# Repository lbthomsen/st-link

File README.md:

# st-link

No longer maintained!

Work in progress - see: https://stm32world.com/wiki/DIY_ST-Link_V2.1

STM32 Programmer.  Should be compatible with ST's ST-Link/V2.1 devices.

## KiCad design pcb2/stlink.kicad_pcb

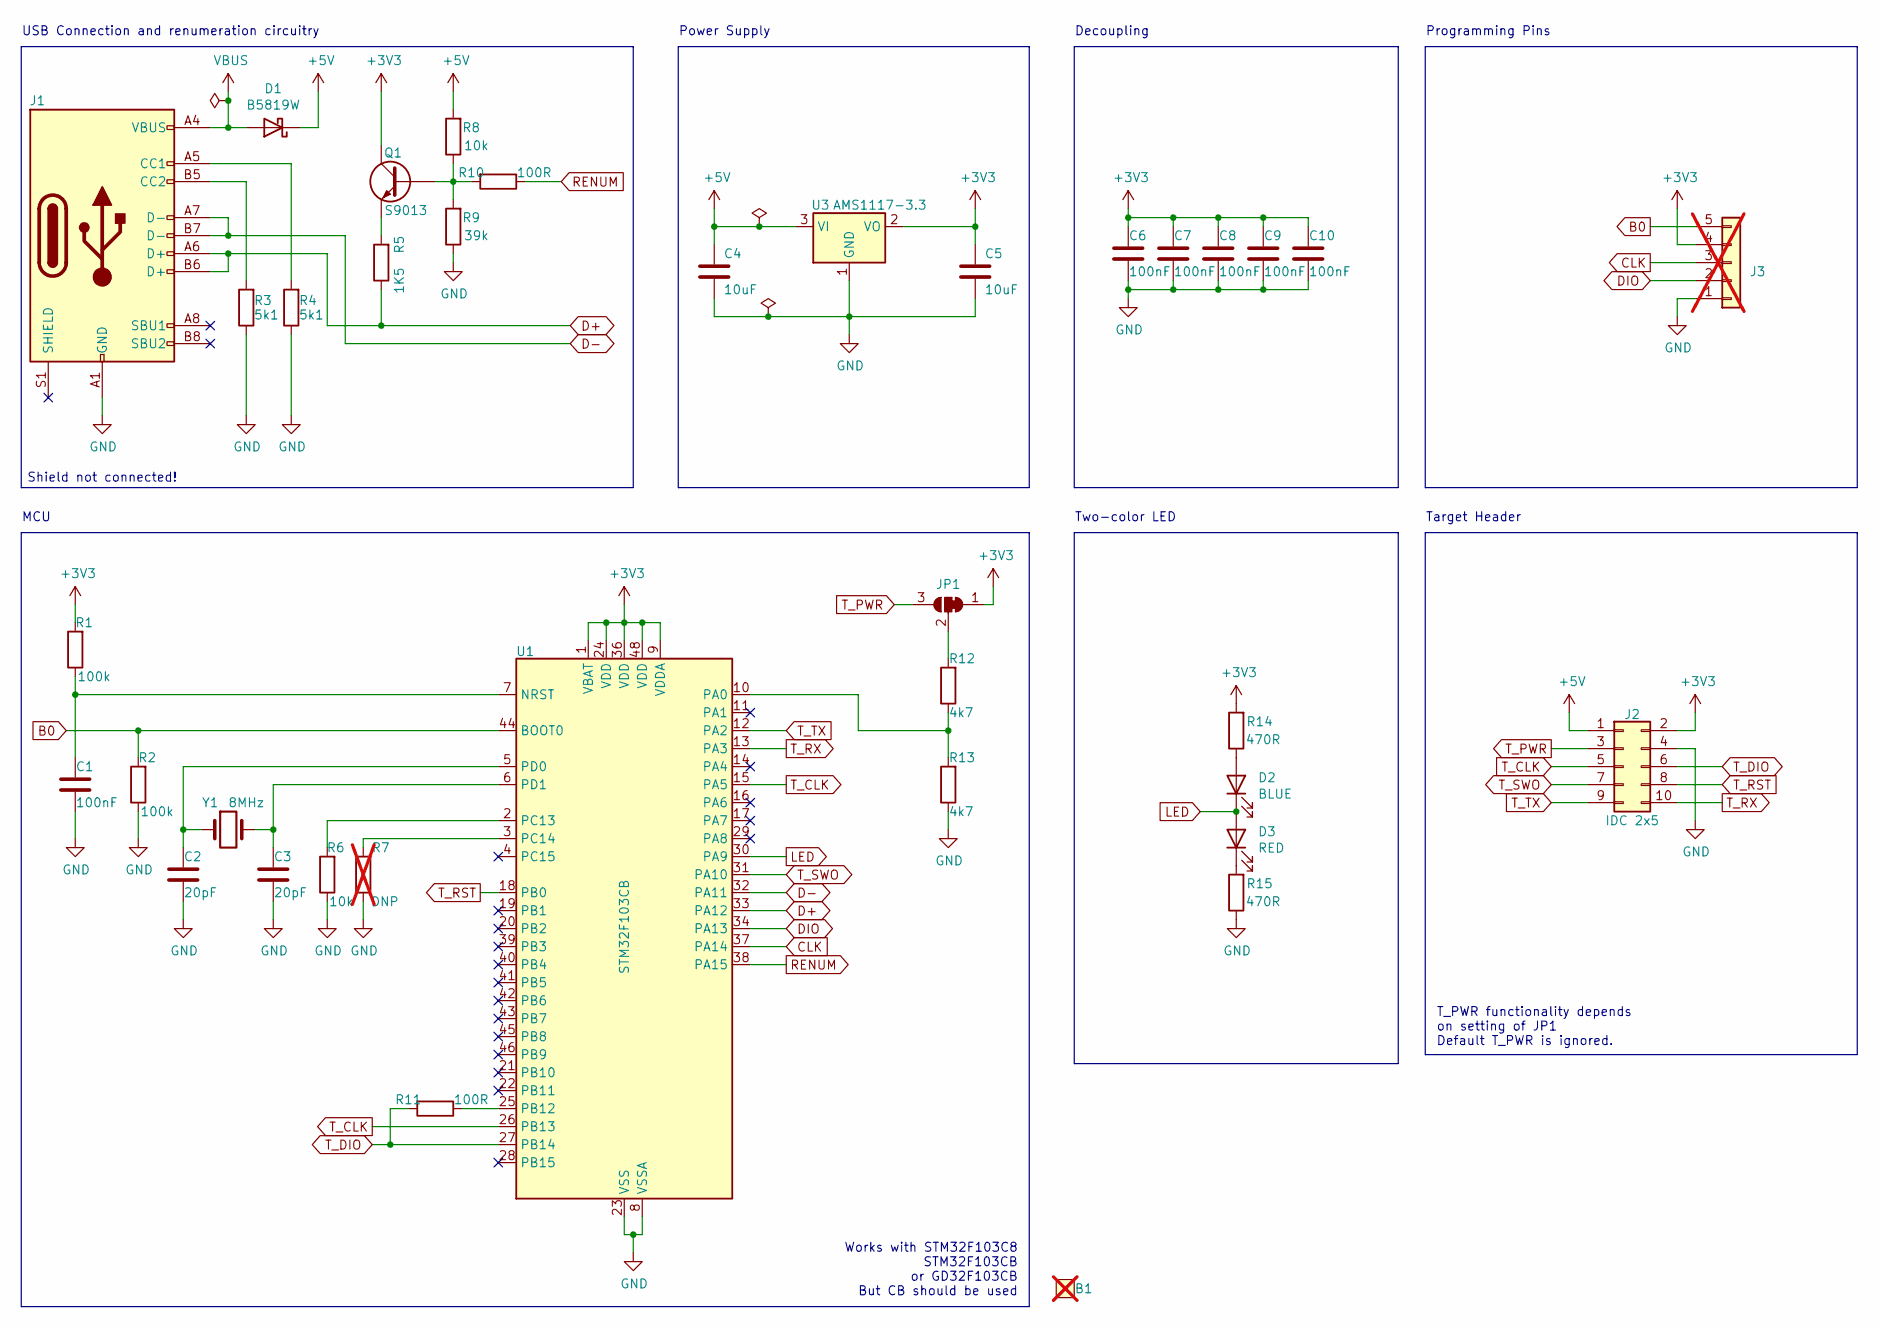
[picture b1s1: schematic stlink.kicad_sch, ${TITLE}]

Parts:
B1: BOARD; not fitted
C1, C6, C7, C8, C9, C10: 100nF; C_0402_1005Metric; LCSC C1525
C2, C3: 20pF; C_0402_1005Metric; LCSC C1554
C4, C5: 10uF; C_0805_2012Metric; LCSC C15850
D1: B5819W; D_SOD-123; LCSC C8598
D2: BLUE; LED_0603_1608Metric; LCSC C72041
D3: RED; LED_0603_1608Metric; LCSC C2286
J1: USB_C_Receptacle_USB2.0-Connector; USB_C_Receptacle_HRO_TYPE-C-31-M-12; LCSC C165948
J2: IDC 2x5; IDC-Header_2x05_P2.54mm_Vertical_SMD; LCSC C41376028
J3: Conn_01x05; PinHeader_1x05_P2.54mm_Vertical; not fitted
JP1: SolderJumper3; SolderJumper-3_P1.3mm_Bridged12_Pad1.0x1.5mm
Q1: S9013; SOT-23; LCSC C6749
R1, R2: 100k; R_0402_1005Metric; LCSC C25741
R3, R4: 5k1; R_0402_1005Metric; LCSC C25905
R5: 1K5; R_0402_1005Metric; LCSC C25867
R6, R8: 10k; R_0402_1005Metric; LCSC C25744
R7: DNP; R_0402_1005Metric; LCSC xxC25744; not fitted
R9: 39k; R_0402_1005Metric; LCSC C25783
R10, R11: 100R; R_0402_1005Metric; LCSC C25076
R12, R13: 4k7; R_0402_1005Metric; LCSC C25900
R14, R15: 470R; R_0402_1005Metric; LCSC C25117
U1: STM32F103CB; LQFP-48_7x7mm_P0.5mm; LCSC C8304
U3: AMS1117-3.3; SOT-223-3_TabPin2; LCSC C6186
Y1: 8MHz; Crystal_SMD_5032-2Pin_5.0x3.2mm; LCSC C115962

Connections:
+3V3: C5.1, C6.1, C7.1, C8.1, C9.1, C10.1, J2.2, J3.4, JP1.1 (A), Q1.C, R1.2, R14.2, U1.1 (VBAT), U1.9 (VDDA), U1.24 (VDD), U1.36 (VDD), U1.48 (VDD), U3.2 (VO)
+5V: C4.1, D1.1 (K), J2.1, R8.2, U3.3 (VI)
B0: J3.5, R2.2, U1.44 (BOOT0)
CLK: J3.3, U1.37 (PA14)
D+: J1.A6 (D+), J1.B6 (D+), R5.1, U1.33 (PA12)
D-: J1.A7 (D-), J1.B7 (D-), U1.32 (PA11)
DIO: J3.2, U1.34 (PA13)
GND: C1.2, C2.2, C3.2, C4.2, C5.2, C6.2, C7.2, C8.2, C9.2, C10.2, J1.A1 (GND), J1.A12 (GND), J1.B1 (GND), J1.B12 (GND), J2.4, J3.1, R2.1, R3.1, R4.1, R6.1, R7.1, R9.1, R13.1, R15.1, U1.8 (VSSA), U1.23 (VSS), U1.35 (VSS), U1.47 (VSS), U3.1 (GND)
LED: D2.1 (K), D3.2 (A), U1.30 (PA9)
unnamed: D2.2 (A), R14.1
unnamed: D3.1 (K), R15.2
unnamed: J1.A5 (CC1), R4.2
unnamed: J1.B5 (CC2), R3.2
unnamed: JP1.2 (C), R12.2
unnamed: Q1.B, R8.1, R9.2, R10.2
unnamed: Q1.E, R5.2
unnamed: C1.1, R1.1, U1.7 (NRST)
unnamed: R12.1, R13.2, U1.10 (PA0)
unnamed: R11.1, U1.25 (PB12)
unnamed: R6.2, U1.2 (PC13)
unnamed: R7.2, U1.3 (PC14)
unnamed: C2.1, U1.5 (PD0), Y1.1
unnamed: C3.1, U1.6 (PD1), Y1.2
RENUM: R10.1, U1.38 (PA15)
T_CLK: J2.5, U1.15 (PA5), U1.26 (PB13)
T_DIO: J2.6, R11.2, U1.27 (PB14)
T_PWR: J2.3, JP1.3 (B)
T_RST: J2.8, U1.18 (PB0)
T_RX: J2.10, U1.13 (PA3)
T_SWO: J2.7, U1.31 (PA10)
T_TX: J2.9, U1.12 (PA2)
VBUS: D1.2 (A), J1.A4 (VBUS), J1.A9 (VBUS), J1.B4 (VBUS), J1.B9 (VBUS)

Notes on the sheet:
Power Supply
T_PWR functionality depends on setting of JP1 Default T_PWR is ignored.
Decoupling
USB Connection and renumeration circuitry
Programming Pins
Target Header
Works with STM32F103C8 STM32F103CB or GD32F103CB But CB should be used
Two-color LED
MCU
Shield not connected!

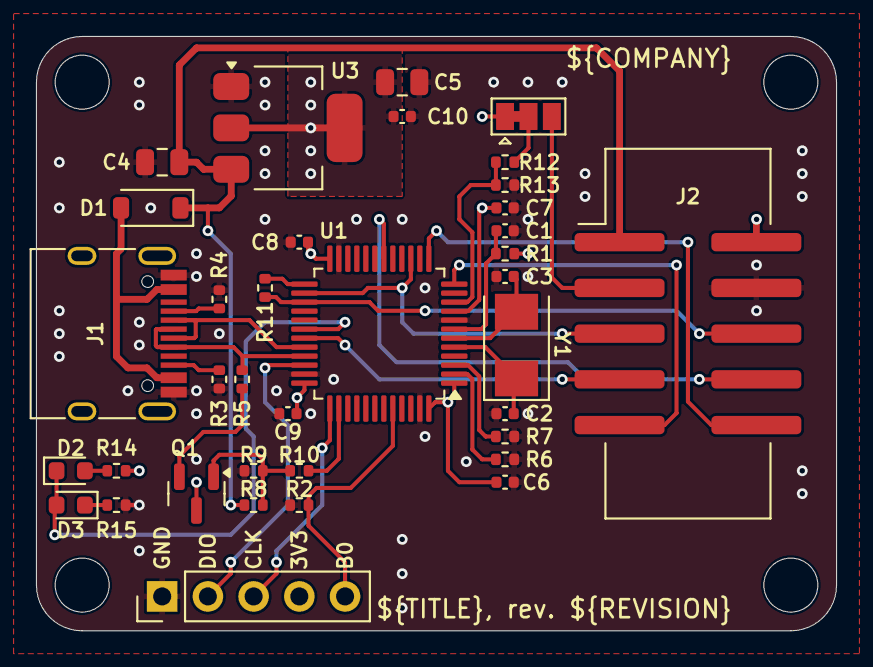
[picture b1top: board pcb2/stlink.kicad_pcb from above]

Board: 4 copper layers, 44.5 x 33.0 mm, 37 parts (0 on the bottom side), 32 nets.

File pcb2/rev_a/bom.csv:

"Reference","Value","Qty","LCSC"
"C1,C6,C7,C8,C9,C10","100nF","6","C1525"
"C2,C3","20pF","2","C1554"
"C4,C5","10uF","2","C15850"
"D1","B5819W","1","C8598"
"D2","BLUE","1","C72041"
"D3","RED","1","C2286"
"J1","USB_C_Receptacle_USB2.0-Connector","1","C165948"
"J2","IDC 2x5","1","C41376028"
"Q1","S9013","1","C6749"
"R1,R2","100k","2","C25741"
"R3,R4","5k1","2","C25905"
"R5","1K5","1","C25867"
"R6,R8","10k","2","C25744"
"R9","39k","1","C25783"
"R10,R11","100R","2","C25076"
"R12,R13","4k7","2","C25900"
"R14,R15","220R","2","C25091"
"U1","STM32F103CB","1","C8304"
"U3","AMS1117-3.3","1","C6186"
"Y1","8MHz","1","C115962"

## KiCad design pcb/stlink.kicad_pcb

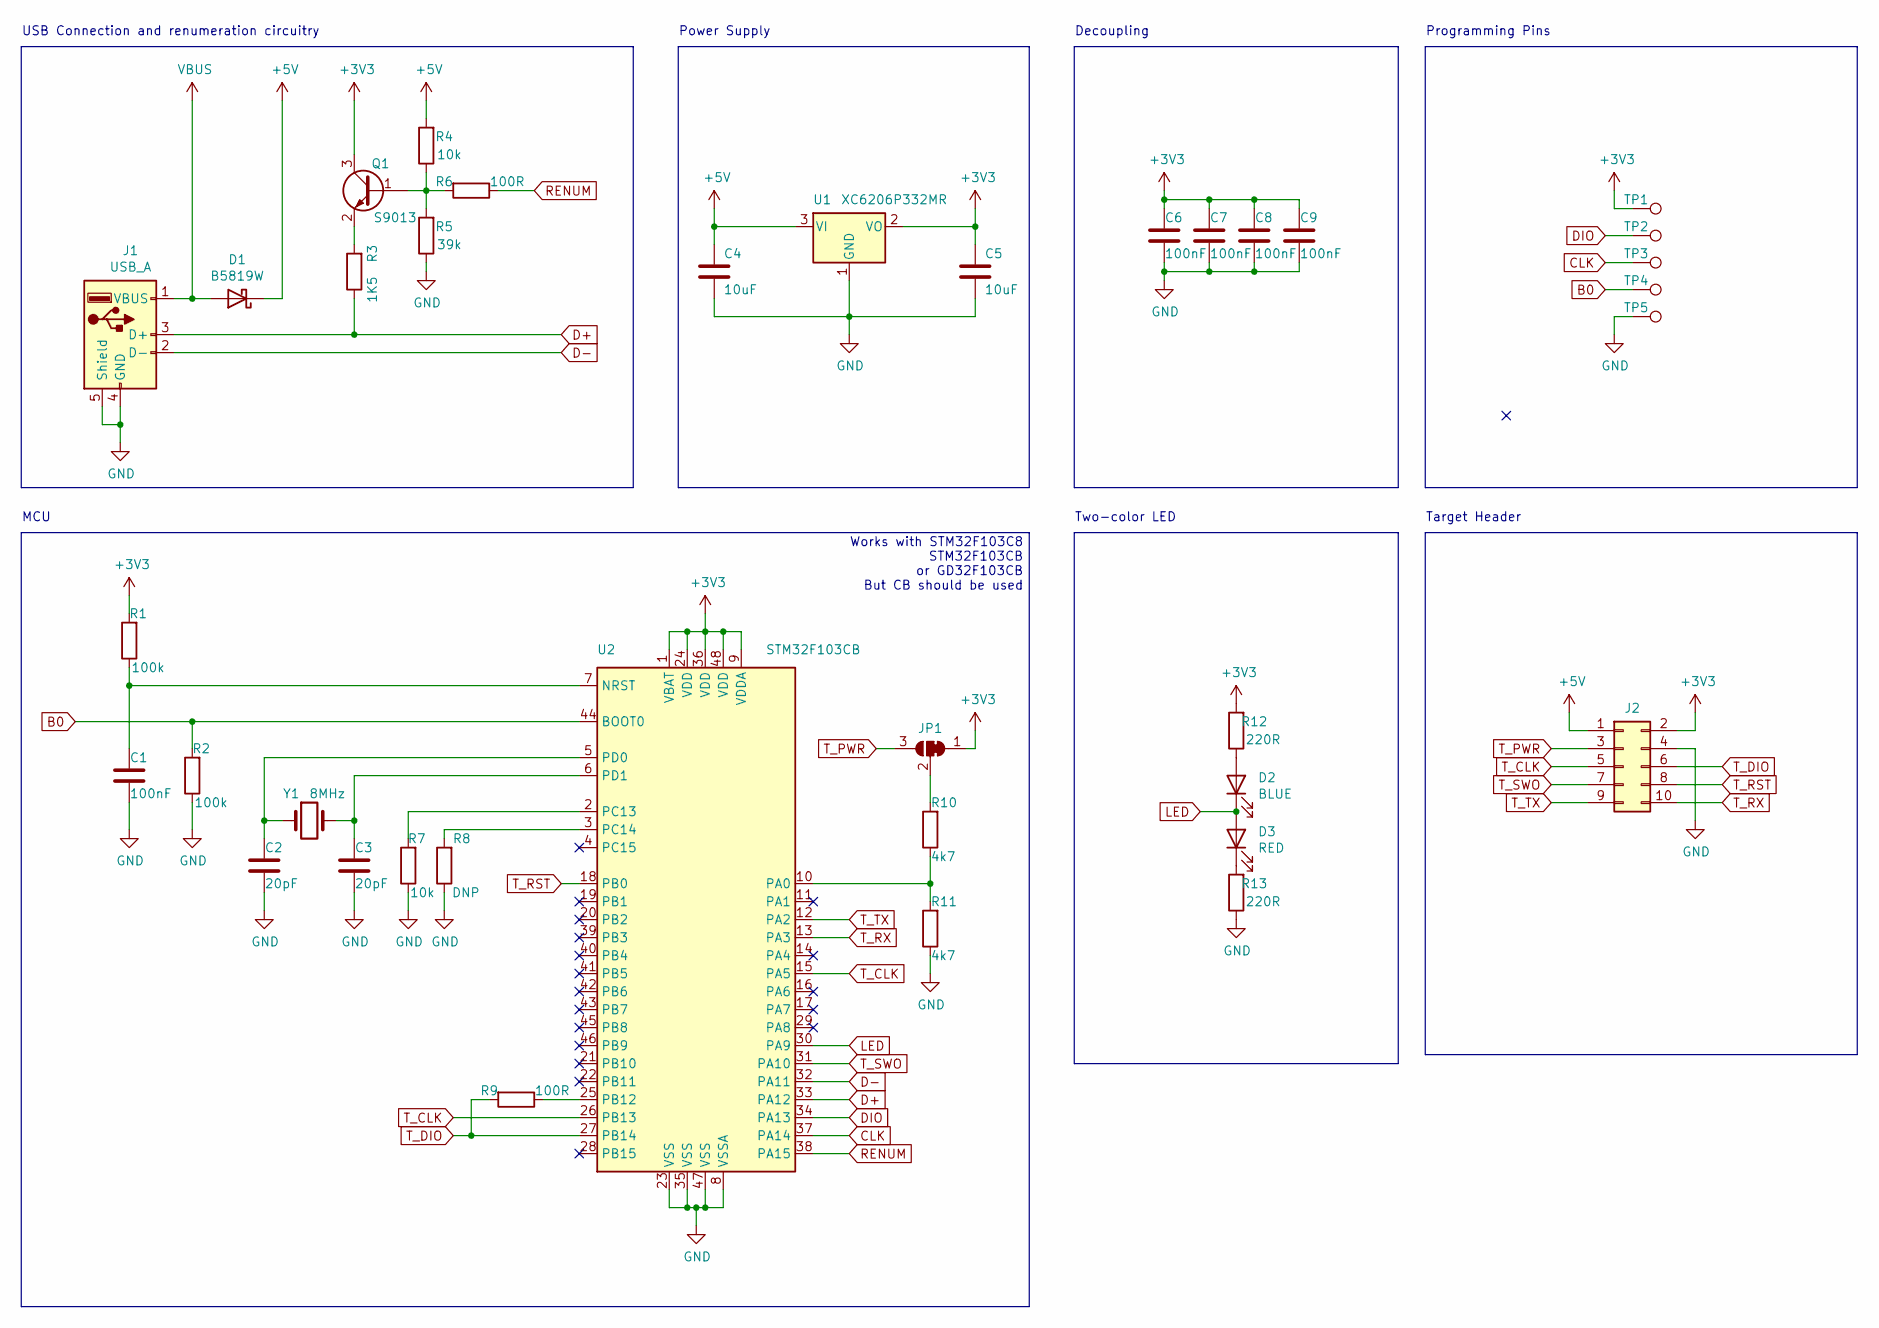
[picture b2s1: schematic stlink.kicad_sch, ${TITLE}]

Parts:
C1, C6, C7, C8, C9: 100nF; C_0402_1005Metric; LCSC C1525
C2, C3: 20pF; C_0402_1005Metric; LCSC C1554
C4, C5: 10uF; C_0805_2012Metric; LCSC C15850
D1: B5819W; D_SOD-123; LCSC C8598
D2: BLUE; LED_0603_1608Metric; LCSC C72041
D3: RED; LED_0603_1608Metric; LCSC C2286
J1: USB_A; USB_Male_A_UP2-AH-1-TH; LCSC C112454
J2: IDC_EDGE
JP1: SolderJumper-3_P1.3mm_Bridged12_Pad1.0x1.5mm
Q1: S9013; SOT-23; LCSC C6749
R1, R2: 100k; R_0402_1005Metric; LCSC C25741
R3: 1K5; R_0402_1005Metric; LCSC C25867
R4, R7: 10k; R_0402_1005Metric; LCSC C25744
R5: 39k; R_0402_1005Metric; LCSC C25783
R6, R9: 100R; R_0402_1005Metric; LCSC C25076
R8: DNP; R_0402_1005Metric; LCSC xxC25744
R10, R11: 4k7; R_0402_1005Metric; LCSC C25900
R12, R13: 220R; R_0402_1005Metric; LCSC C25091
TP1, TP2, TP3, TP4, TP5: TestPoint_Pad_1.0x1.0mm
U1: XC6206P332MR; SOT-23; LCSC C5446
U2: STM32F103CB; LQFP-48_7x7mm_P0.5mm; LCSC C8304
Y1: 8MHz; Crystal_SMD_5032-2Pin_5.0x3.2mm; LCSC C115962

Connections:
+3V3: C5.1, C6.1, C7.1, C8.1, C9.1, J2.2, JP1.1 (A), Q1.3 (C), R1.2, R12.2, TP1.1, U1.2 (VO), U2.1 (VBAT), U2.9 (VDDA), U2.24 (VDD), U2.36 (VDD), U2.48 (VDD)
+5V: C4.1, D1.1 (K), J2.1, R4.2, U1.3 (VI)
B0: R2.2, TP4.1, U2.44 (BOOT0)
CLK: TP3.1, U2.37 (PA14)
D+: J1.3 (D+), R3.1, U2.33 (PA12)
D-: J1.2 (D-), U2.32 (PA11)
DIO: TP2.1, U2.34 (PA13)
GND: C1.2, C2.2, C3.2, C4.2, C5.2, C6.2, C7.2, C8.2, C9.2, J1.4 (GND), J1.5 (Shield), J2.4, R2.1, R5.1, R7.1, R8.1, R11.1, R13.1, TP5.1, U1.1 (GND), U2.8 (VSSA), U2.23 (VSS), U2.35 (VSS), U2.47 (VSS)
LED: D2.1 (K), D3.2 (A), U2.30 (PA9)
unnamed: C1.1, R1.1, U2.7 (NRST)
unnamed: C2.1, U2.5 (PD0), Y1.1
unnamed: C3.1, U2.6 (PD1), Y1.2
unnamed: D2.2 (A), R12.1
unnamed: D3.1 (K), R13.2
unnamed: JP1.2 (C), R10.2
unnamed: Q1.1 (B), R4.1, R5.2, R6.2
unnamed: Q1.2 (E), R3.2
unnamed: R7.2, U2.2 (PC13)
unnamed: R8.2, U2.3 (PC14)
unnamed: R9.1, U2.25 (PB12)
unnamed: R10.1, R11.2, U2.10 (PA0)
RENUM: R6.1, U2.38 (PA15)
T_CLK: J2.5, U2.15 (PA5), U2.26 (PB13)
T_DIO: J2.6, R9.2, U2.27 (PB14)
T_PWR: J2.3, JP1.3 (B)
T_RST: J2.8, U2.18 (PB0)
T_RX: J2.10, U2.13 (PA3)
T_SWO: J2.7, U2.31 (PA10)
T_TX: J2.9, U2.12 (PA2)
VBUS: D1.2 (A), J1.1 (VBUS)

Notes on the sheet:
Power Supply
Decoupling
USB Connection and renumeration circuitry
Programming Pins
Target Header
Works with STM32F103C8 STM32F103CB or GD32F103CB But CB should be used
Two-color LED
MCU

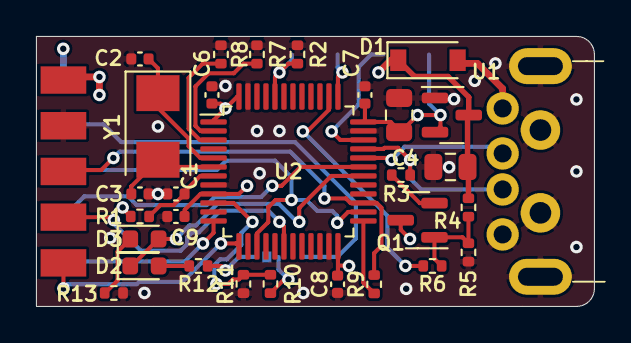
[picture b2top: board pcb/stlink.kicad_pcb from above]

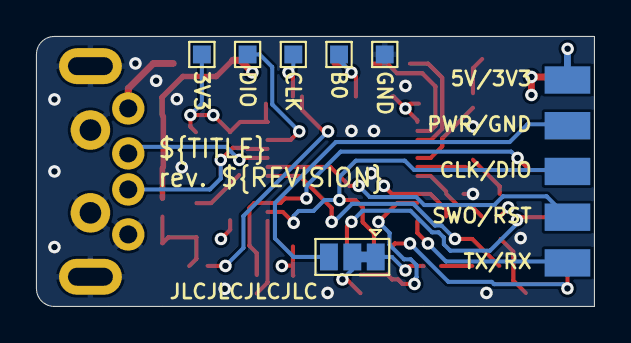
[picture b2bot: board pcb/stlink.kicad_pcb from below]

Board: 4 copper layers, 31.0 x 15.0 mm, 37 parts (7 on the bottom side), 30 nets.

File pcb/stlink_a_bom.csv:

Comment,Designator,Footprint,LCSC
"20pF","C2,C3","Capacitor_SMD:C_0402_1005Metric","C1554"
"10uF","C4,C5","Capacitor_SMD:C_0805_2012Metric","C15850"
"100nF","C6,C7,C8,C9,C1","Capacitor_SMD:C_0402_1005Metric","C1525"
"B5819W","D1","Diode_SMD:D_SOD-123","C8598"
"GREEN","D2","LED_SMD:LED_0603_1608Metric","C72043"
"RED","D3","LED_SMD:LED_0603_1608Metric","C2286"
"MouseBite","H4,H3,H2,H1","st-link:mouse-bite-1mm-slot"
"USB_A","J1","st-link:USB_Male_A_UP2-AH-1-TH"
"~","J2","st-link:IDC_EDGE"
"S9013","Q1","Package_TO_SOT_SMD:SOT-23","C6749"
"100k","R1,R2","Resistor_SMD:R_0402_1005Metric","C25741"
"4k7","R11,R10","Resistor_SMD:R_0402_1005Metric","C25900"
"220R","R12,R13","Resistor_SMD:R_0402_1005Metric","C25091"
"1K5","R3","Resistor_SMD:R_0402_1005Metric","C25867"
"10k","R4,R7","Resistor_SMD:R_0402_1005Metric","C25744"
"33k","R5","Resistor_SMD:R_0402_1005Metric","C25779"
"100R","R6,R9","Resistor_SMD:R_0402_1005Metric","C25076"
"NP","R8","Resistor_SMD:R_0402_1005Metric","xxC25744"
"~","TP2,TP3,TP1,TP4,TP5","TestPoint:TestPoint_Pad_D1.0mm"
"XC6206P332MR","U1","Package_TO_SOT_SMD:SOT-23","C5446"
"GD32F103CBT6","U2","Package_QFP:LQFP-48_7x7mm_P0.5mm","C77979"
"8MHz","Y1","Crystal:Crystal_SMD_5032-2Pin_5.0x3.2mm","C115962"

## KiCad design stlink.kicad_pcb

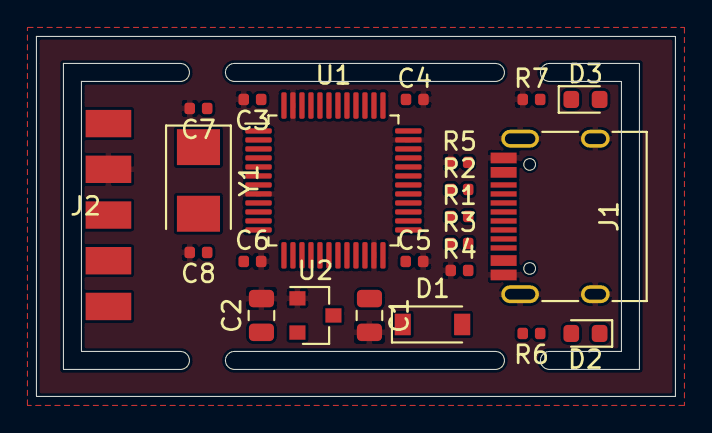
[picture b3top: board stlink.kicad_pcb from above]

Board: 2 copper layers, 35.5 x 20.0 mm, 23 parts (0 on the bottom side), 17 nets, no tracks yet.

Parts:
C1, C2: 10uF; C_0805_2012Metric
C3, C4, C5, C6: 100nF; C_0402_1005Metric
C7, C8: 20pF; C_0402_1005Metric
D1: B5819W; D_SOD-123
D2: GREEN; LED_0603_1608Metric
D3: RED; LED_0603_1608Metric
J1: USB_C_Receptacle_USB2.0; USB_C_Receptacle_HRO_TYPE-C-31-M-12
J2: IDC_EDGE
R1, R2: 10R; R_0402_1005Metric
R3: 1K5; R_0402_1005Metric
R4, R5: 5k1; R_0402_1005Metric
R6, R7: 1k; R_0402_1005Metric
U1: STM32F103C8Tx; LQFP-48_7x7mm_P0.5mm
U2: XC6206P332MR; SOT-23
Y1: Crystal; Crystal_SMD_5032-2Pin_5.0x3.2mm

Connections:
+3V3: C2.1, C3.1, C4.1, C5.1, C6.1, R3.1, R6.2, U2.2
+5V: C1.1, D1.1, U2.3
D+: R2.1, U1.33
D-: R1.1, U1.32
GND: C1.2, C2.2, C3.2, C4.2, C5.2, C6.2, C7.2, C8.2, J1.A1, J1.A12, J1.B1, J1.B12, J1.S1, J2.7, R4.1, R5.1, R7.1, U1.8, U1.23, U1.35, U1.47, U2.1
JTCK_SWCLK: J2.4, U1.37
LED: D2.1, D3.2
unnamed: C7.1, U1.5, Y1.1
unnamed: C8.1, U1.6, Y1.2
unnamed: D2.2, R6.1
unnamed: D3.1, R7.2
unnamed: J1.A5, R4.2
unnamed: J1.A6, J1.B6, R2.2, R3.2
unnamed: J1.A7, J1.B7, R1.2
unnamed: J1.B5, R5.2
unnamed: U1.1, U1.9, U1.24, U1.36, U1.48
VBUS: D1.2, J1.A4, J1.A9, J1.B4, J1.B9

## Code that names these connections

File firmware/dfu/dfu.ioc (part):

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Mcu.Name=STM32F103C(8-B)Tx
Mcu.Package=LQFP48
Mcu.UserName=STM32F103C8Tx
PA11.Mode=Device
PA11.Signal=USB_DM
PA12.Mode=Device
PA12.Signal=USB_DP
PA13.Mode=Serial_Wire
PA13.Signal=SYS_JTMS-SWDIO
PA14.Mode=Serial_Wire
PA14.Signal=SYS_JTCK-SWCLK
PC13-TAMPER-RTC.GPIOParameters=PinState,GPIO_Label
PC13-TAMPER-RTC.GPIO_Label=LED
PC13-TAMPER-RTC.PinState=GPIO_PIN_SET
PC13-TAMPER-RTC.Signal=GPIO_Output
PD0-OSC_IN.Mode=HSE-External-Oscillator
PD0-OSC_IN.Signal=RCC_OSC_IN
PD1-OSC_OUT.Mode=HSE-External-Oscillator
PD1-OSC_OUT.Signal=RCC_OSC_OUT
RCC.SYSCLKFreq_VALUE=72000000
RCC.SYSCLKSource=RCC_SYSCLKSOURCE_PLLCLK
board=custom

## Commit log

2020-06-29 Hmmm
2021-07-11 Hmmmm
2021-07-12 Order rev a
2021-07-13 Minor tweaks
2021-07-22 Removed bak and cache files
2021-11-02 Cosmetic changes
2022-08-03 Should be ready to order
2022-08-05 Ordered rev_d
2022-08-06 Bumped revision to e (d ordered)
2022-08-12 Flipped silk screen designator
2022-10-18 Rev e order
2022-10-18 Pushed new revision due to changed jlcpcb requirements.
2023-04-16 Exported rev g - not ordered yet
2023-04-29 Added framework for simple dfu bootstrap
2025-03-16 DFU Bootloader should be working
2025-03-17 Playing with bootloader
2025-03-19 DFU Boot working
2025-07-16 Added appropriate blackmagic firmware to use with st-link bootloader
2025-08-10 Working on version 2
2025-08-10 Hmmmmm
2025-08-11 Switching workstation
2025-09-16 Order files ready for pcb2
2025-09-16 Syncing cover and pcb2
2025-09-16 Tweaks
2025-09-16 BUG in jobset
2025-09-17 Retried jobset export
2025-09-22 Ready to order
2025-09-23 Ready for order
2025-09-24 Jolt Connect rev. a files ready
2025-09-28 Started rev_b
2025-10-08 New build
2025-10-10 Cleanup
2025-10-10 More cleanup
